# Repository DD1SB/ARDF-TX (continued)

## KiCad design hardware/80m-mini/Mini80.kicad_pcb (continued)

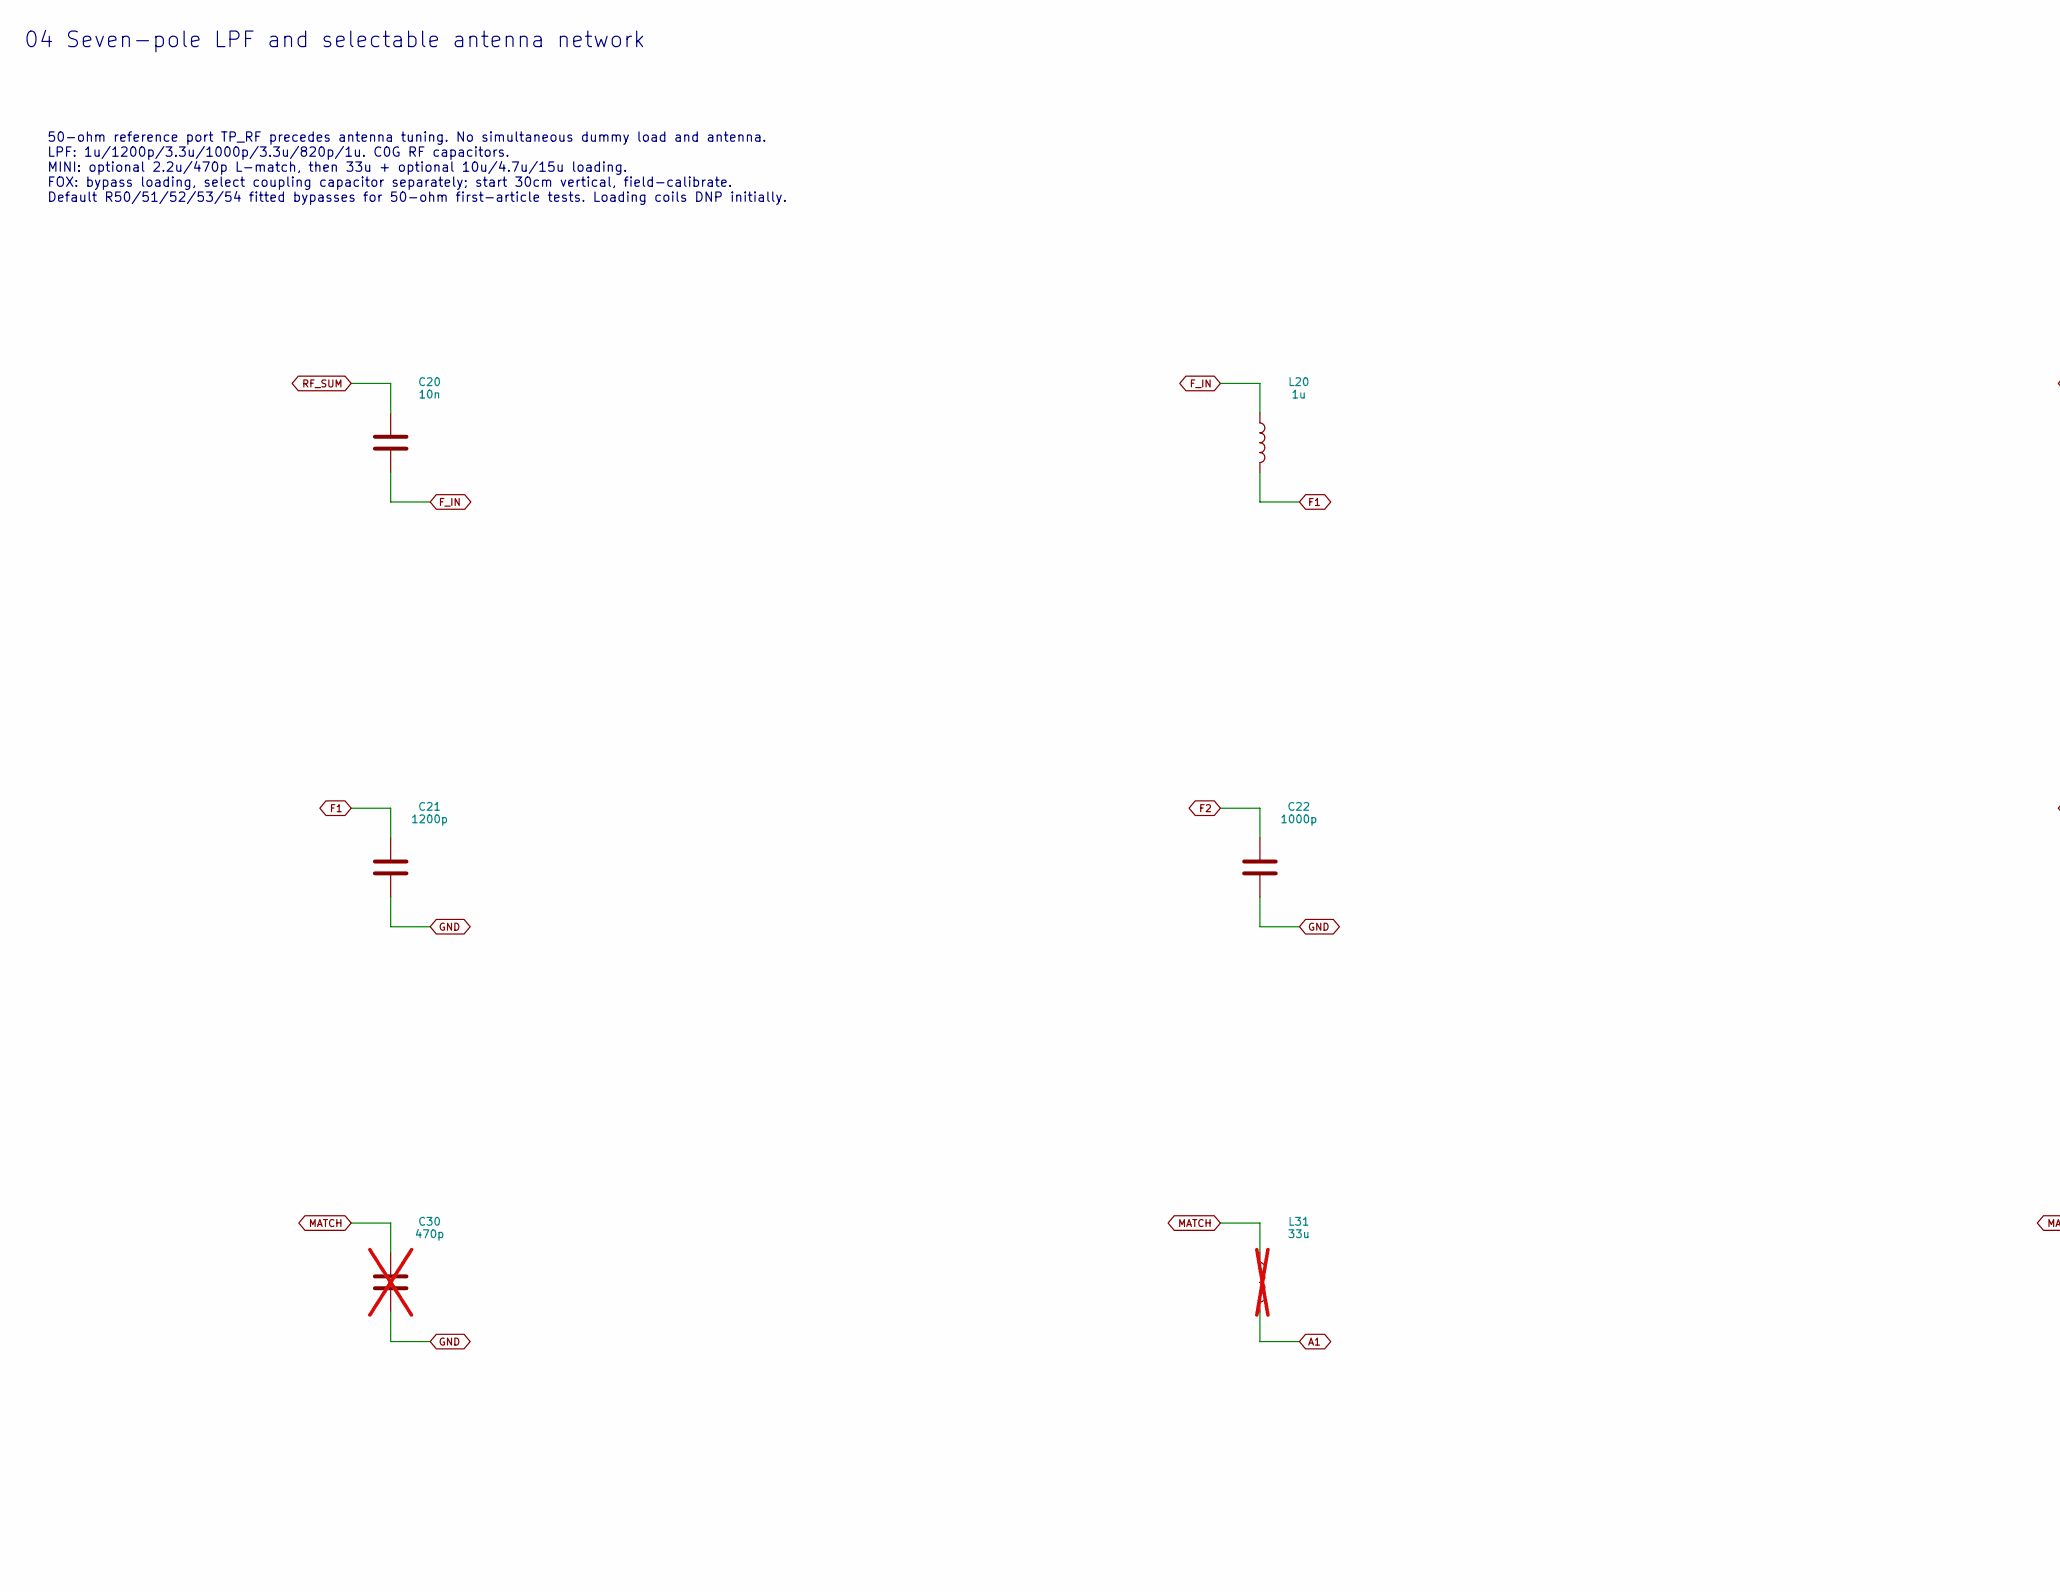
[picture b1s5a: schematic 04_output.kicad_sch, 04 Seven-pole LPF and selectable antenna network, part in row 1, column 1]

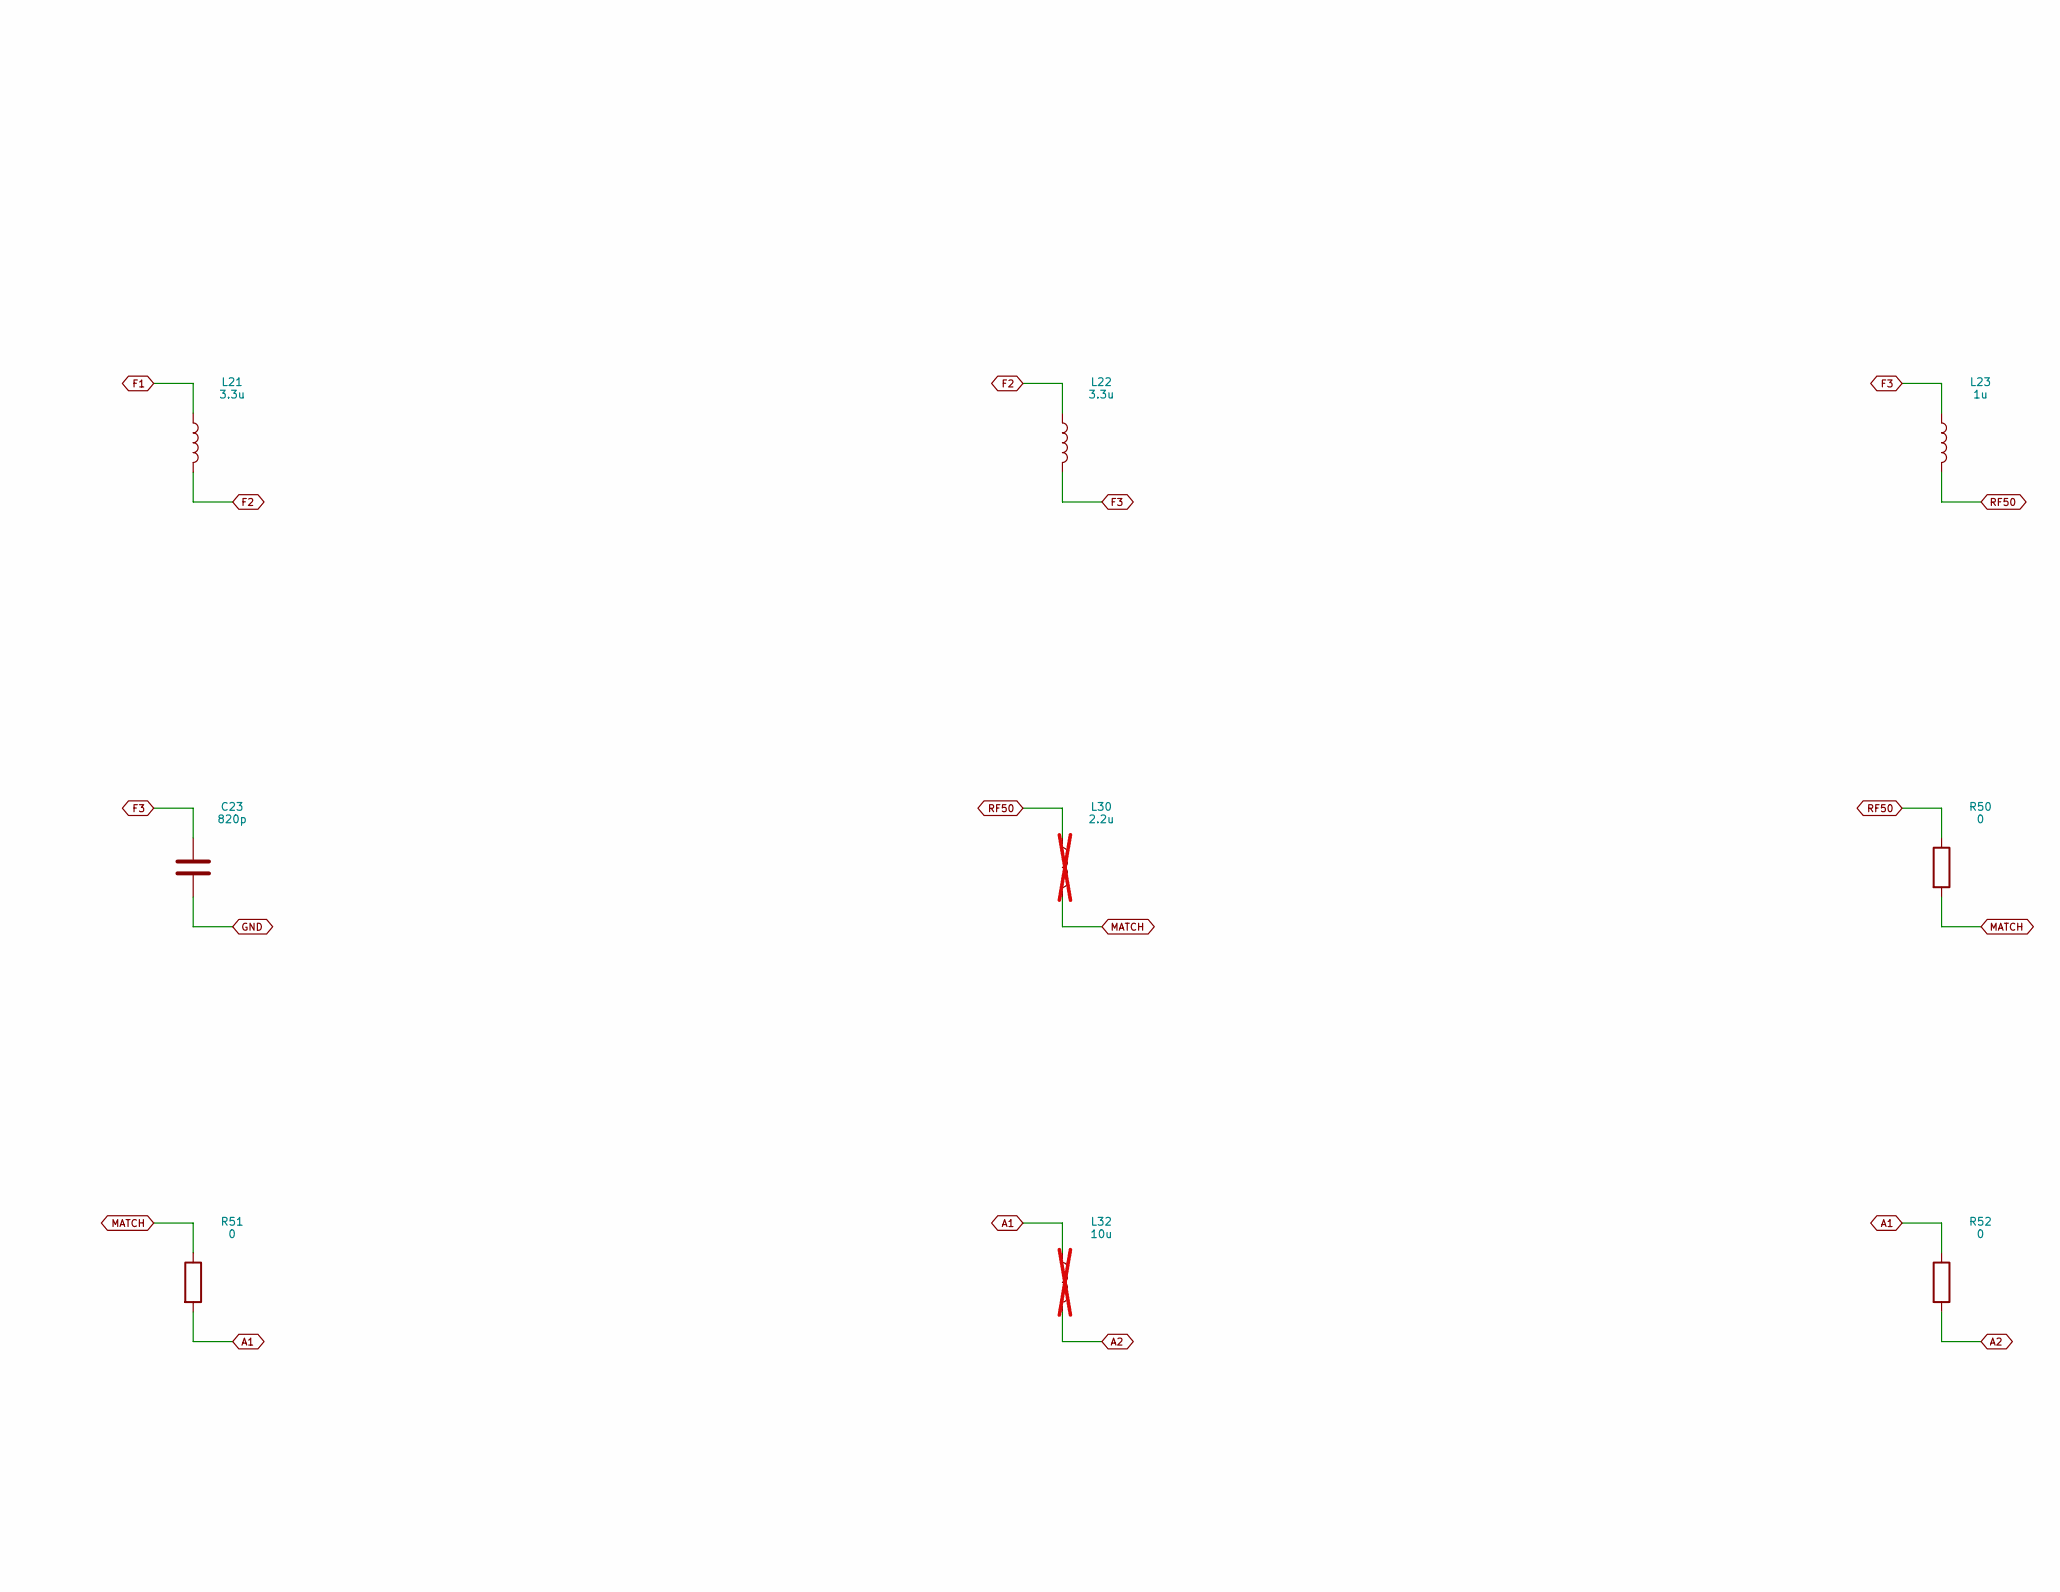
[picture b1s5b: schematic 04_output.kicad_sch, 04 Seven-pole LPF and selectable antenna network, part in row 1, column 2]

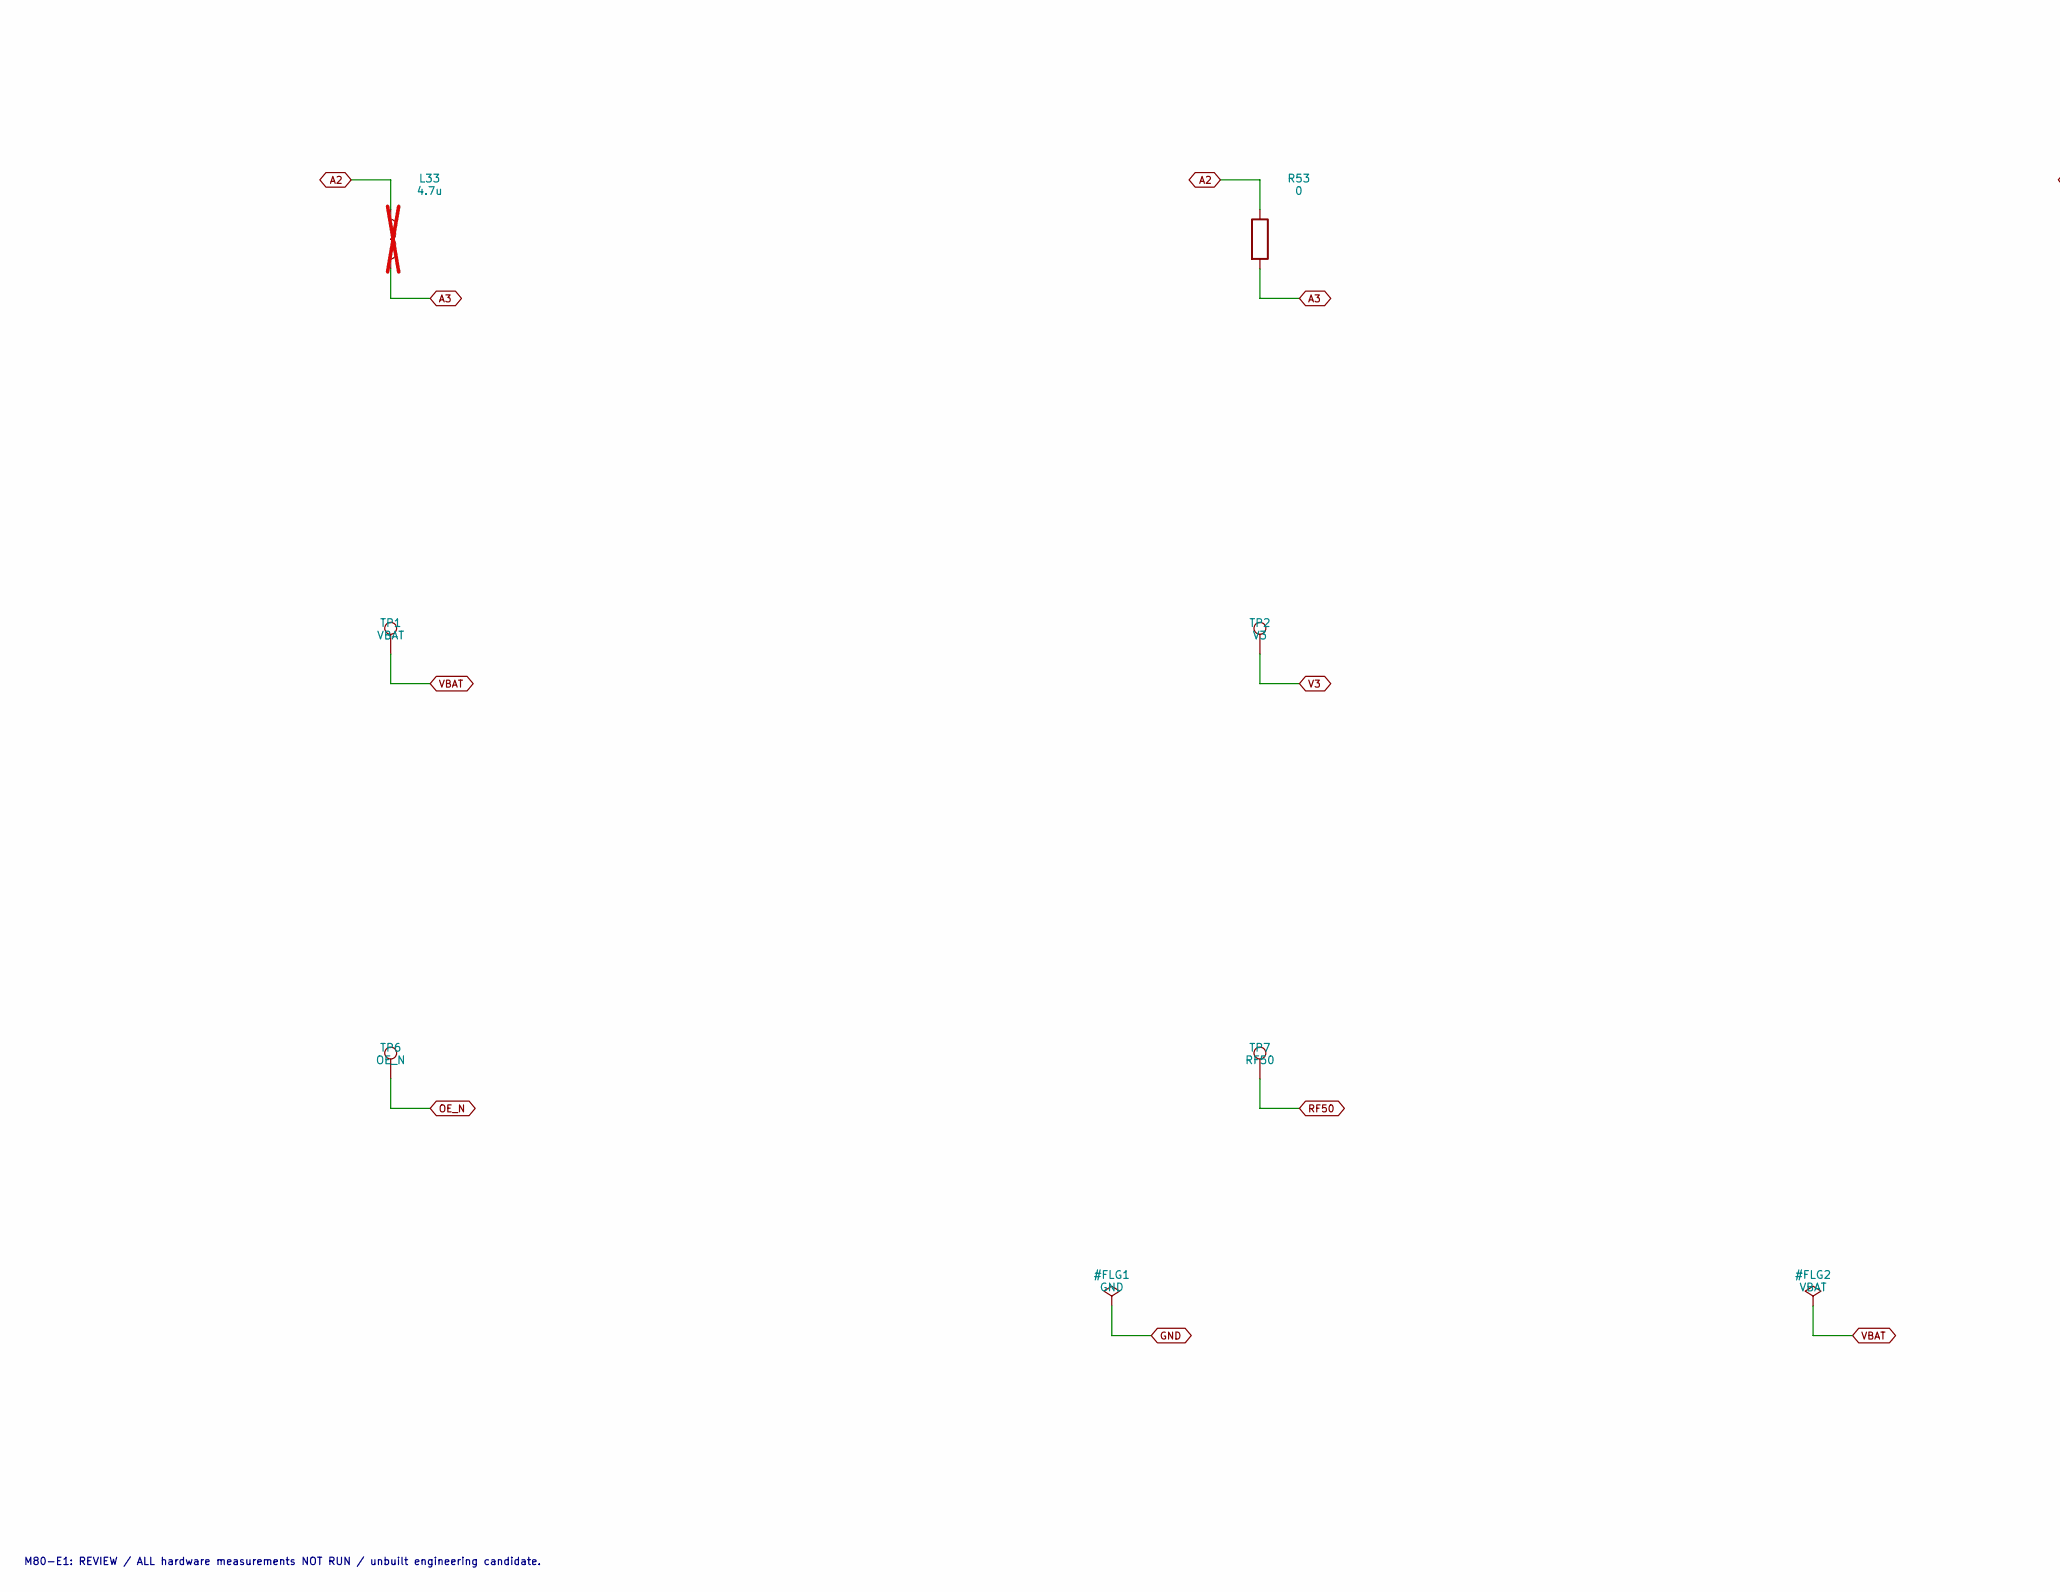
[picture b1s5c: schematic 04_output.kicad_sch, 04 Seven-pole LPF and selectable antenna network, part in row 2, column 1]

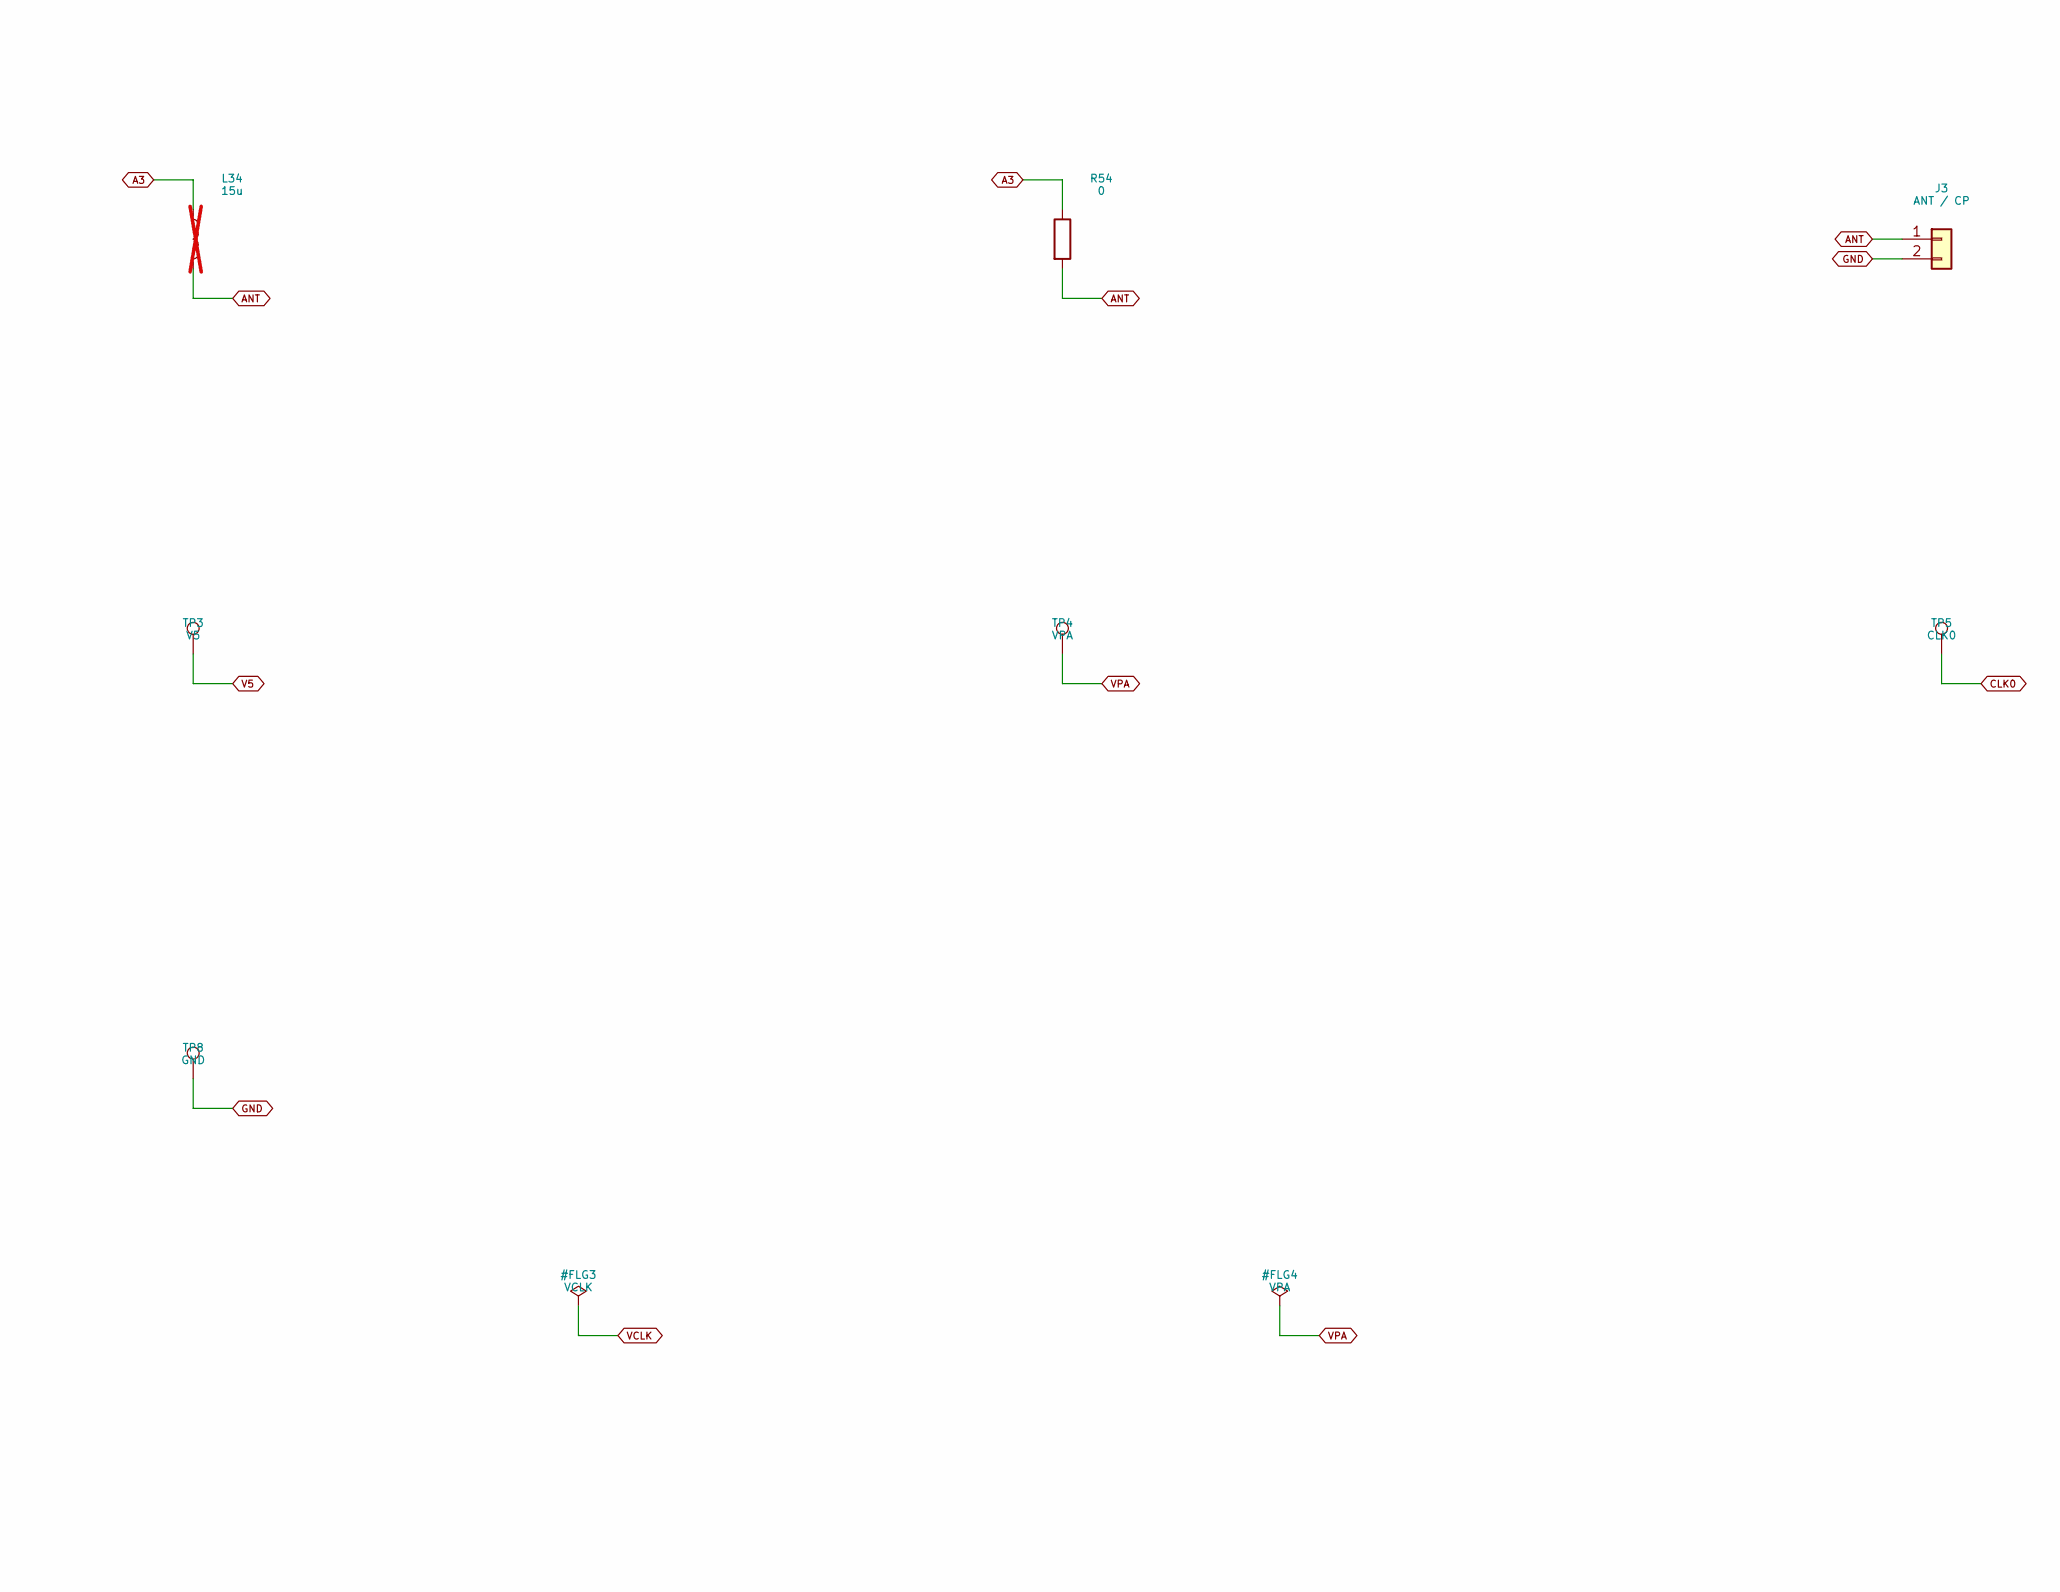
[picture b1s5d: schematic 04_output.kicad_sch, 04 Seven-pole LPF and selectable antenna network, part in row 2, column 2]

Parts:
C20: 10n; C_0603_1608Metric; MPN GRM1885C1H103JA01D
C21: 1200p; C_0603_1608Metric; MPN GRM1885C1H122JA01D
C22: 1000p; C_0603_1608Metric; MPN GRM1885C1H102JA01D
C23: 820p; C_0603_1608Metric; MPN GRM1885C1H821JA01D
C30: 470p; C_0603_1608Metric; MPN GRM1885C1H471JA01D; not fitted
J3: ANT / CP; Wire2; MPN Soldered strain-relieved wire
L20, L23: 1u; Coilcraft_1008LS; MPN 1008LS-102XJRC
L21, L22: 3.3u; Coilcraft_1008LS; MPN 1008LS-332XJRC
L30: 2.2u; Coilcraft_1008LS; MPN 1008LS-222XJRC; not fitted
L31: 33u; Coilcraft_1812LS; MPN 1812LS-333XJRC; not fitted
L32: 10u; Coilcraft_1008LS; MPN 1008LS-103XJRC; not fitted
L33: 4.7u; Coilcraft_1008LS; MPN 1008LS-472XJRC; not fitted
L34: 15u; Coilcraft_1812LS; MPN 1812LS-153XJRC; not fitted
R50, R51, R52, R53, R54: 0; R_0402_1005Metric; MPN RC0402JR-070RL
TP1: VBAT; TestPoint_Pad_D1.0mm; MPN PCB feature
TP2: V3; TestPoint_Pad_D1.0mm; MPN PCB feature
TP3: V5; TestPoint_Pad_D1.0mm; MPN PCB feature
TP4: VPA; TestPoint_Pad_D1.0mm; MPN PCB feature
TP5: CLK0; TestPoint_Pad_D1.0mm; MPN PCB feature
TP6: OE_N; TestPoint_Pad_D1.0mm; MPN PCB feature
TP7: RF50; TestPoint_Pad_D1.0mm; MPN PCB feature
TP8: GND; TestPoint_Pad_D1.0mm; MPN PCB feature

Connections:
A1: L31.2, L32.1, R51.2, R52.1
A2: L32.2, L33.1, R52.2, R53.1
A3: L33.2, L34.1, R53.2, R54.1
ANT: J3.1, L34.2, R54.2
CLK0: TP5.1; also elsewhere on the board
F1: C21.1, L20.2, L21.1
F2: C22.1, L21.2, L22.1
F3: C23.1, L22.2, L23.1
F_IN: C20.2, L20.1
GND: C21.2, C22.2, C23.2, C30.2, J3.2, TP8.1; also elsewhere on the board
MATCH: C30.1, L30.2, L31.1, R50.2, R51.1
OE_N: TP6.1; also elsewhere on the board
RF50: L23.2, L30.1, R50.1, TP7.1
RF_SUM: C20.1; also elsewhere on the board
V3: TP2.1; also elsewhere on the board
V5: TP3.1; also elsewhere on the board
VBAT: TP1.1; also elsewhere on the board
VPA: TP4.1; also elsewhere on the board

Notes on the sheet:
04 Seven-pole LPF and selectable antenna network
50-ohm reference port TP_RF precedes antenna tuning. No simultaneous dummy load and antenna. LPF: 1u/1200p/3.3u/1000p/3.3u/820p/1u. C0G RF capacitors. MINI: optional 2.2u/470p L-match, then 33u + optional 10u/4.7u/15u loading. FOX: bypass loading, select coupling capacitor separately; start 30cm ve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
M80-E1: REVIEW / ALL hardware measurements NOT RUN / unbuilt engineering candidate.

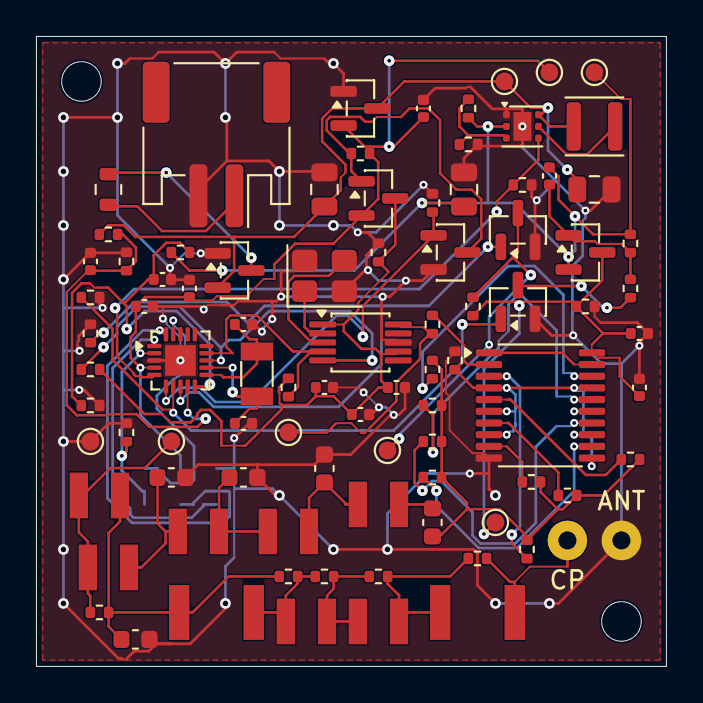
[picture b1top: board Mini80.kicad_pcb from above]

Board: 2 copper layers, 35.0 x 35.0 mm, 92 parts (1 on the bottom side), 51 nets.

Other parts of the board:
H1, H2: MountingHole_2.2mm_M2

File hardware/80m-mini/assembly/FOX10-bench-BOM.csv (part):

ref,value,mpn,footprint,population,note,price_basis,supplier,source_url
J1,BAT 1S,S2B-PH-SM4-TB(LF)(SN),Connector_JST:JST_PH_S2B-PH-SM4-TB_1x02-1MP_P2.00mm_Horizontal,ALL,Pin 1 +. Verify purchased battery harness polarity.,"BUDGET ALLOWANCE, NOT A QUOTE",OPEN,
F1,200mA PPTC,MF-FSMF020X-2,Mini80:MF_FSMF0603,ALL,200 mA hold / protected cell remains mandatory.,CATALOG OBSERVATION,DigiKey,https://www.digikey.com/en/products/detail/bourns-inc/MF-FSM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
Q1,DMP2035U,DMP2035U-7,Package_TO_SOT_SMD:SOT-23,ALL,"Reverse polarity: drain battery, source protected rail.",CATALOG OBSERVATION,LCSC C110499,https://lcsc.com/product-detail/MOSFETs_Diodes-Incorporated-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
C1,10u,GRM21BR61C106KE15L,Capacitor_SMD:C_0805_2012Metric,ALL,,"BUDGET ALLOWANCE, NOT A QUOTE",OPEN,
U1,MCP1700 3.0V,MCP1700T-3002E/TT,Package_TO_SOT_SMD:SOT-23,ALL,1.6 uA typical IQ; 6 V maximum supply.,CATALOG OBSERVATION,LCSC C62244,https://www.lcsc.com/product-image/C62244.html
C2,1u,GRM155R61A105KE15D,Capacitor_SMD:C_0402_1005Metric,ALL,,"BUDGET ALLOWANCE, NOT A QUOTE",OPEN,
U2,TPS61099DRVR,TPS61099DRVR,Package_SON:WSON-6-1EP_2x2mm_P0.65mm_EP1x1.6mm,ALL,"1V feedback; 390k/100k gives 4.90V PWM, ~5.05V PFM.",CATALOG OBSERVATION,LCSC C2842395,https://www.lcsc.com/product-image/C2842395.html
L1,2.2u power,SWPA3015S2R2MT,Inductor_SMD:L_Sunlord_SWPA3015S,ALL,"2.2 uH, saturation >=1.5 A. Short boost loop.","BUDGET ALLOWANCE, NOT A QUOTE",OPEN,
C3,10u,GRM21BR61C106KE15L,Capacitor_SMD:C_0805_2012Metric,ALL,,"BUDGET ALLOWANCE, NOT A QUOTE",OPEN,
C4,22u,GRM21BR61A226ME44L,Capacitor_SMD:C_0805_2012Metric,ALL,Derated effective capacitance must exceed 8uF.,"BUDGET ALLOWANCE, NOT A QUOTE",OPEN,
R1,390k,RC0402FR-07390KL,Resistor_SMD:R_0402_1005Metric,ALL,,"BUDGET ALLOWANCE, NOT A QUOTE",OPEN,
R2,100k,RC0402FR-07100KL,Resistor_SMD:R_0402_1005Metric,ALL,,"BUDGET ALLOWANCE, NOT A QUOTE",OPEN,
R3,100k,RC0402FR-07100KL,Resistor_SMD:R_0402_1005Metric,ALL,,"BUDGET ALLOWANCE, NOT A QUOTE",OPEN,
Q2,CLOCK supply,DMP2035U-7,Package_TO_SOT_SMD:SOT-23,ALL,,CATALOG OBSERVATION,LCSC C110499,https://lcsc.com/product-detail/MOSFETs_Diodes-Incorporated-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
R4,100k,RC0402FR-07100KL,Resistor_SMD:R_0402_1005Metric,ALL,,"BUDGET ALLOWANCE, NOT A QUOTE",OPEN,
Q3,CLOCK enable,"2N7002,215",Package_TO_SOT_SMD:SOT-23,ALL,,"BUDGET ALLOWANCE, NOT A QUOTE",OPEN,https://assets.nexperia.com/documents/data-sheet/2N7002.pdf
R5,100k,RC0402FR-07100KL,Resistor_SMD:R_0402_1005Metric,ALL,,"BUDGET ALLOWANCE, NOT A QUOTE",OPEN,
R6,100k,RC0402FR-07100KL,Resistor_SMD:R_0402_1005Metric,ALL,Discharge clock rail after shutdown.,"BUDGET ALLOWANCE, NOT A QUOTE",OPEN,
R7,2M,RC0402FR-072ML,Resistor_SMD:R_0402_1005Metric,ALL,,"BUDGET ALLOWANCE, NOT A QUOTE",OPEN,
R8,1M,RC0402FR-071ML,Resistor_SMD:R_0402_1005Metric,ALL,,"BUDGET ALLOWANCE, NOT A QUOTE",OPEN,
C5,10n,GRM155R71H103KA88D,Capacitor_SMD:C_0402_1005Metric,ALL,Use internal 1.5V reference; long acquisition; VBAT=3*Vadc.,"BUDGET ALLOWANCE, NOT A QUOTE",OPEN,
U3,ATtiny1616-MNR,ATTINY1616-MNR,Mini80:ATtiny1616_VQFN20_JLC,ALL,,CATALOG OBSERVATION,Mouser,https://www.mouser.com/en/ProductDetail/Microchip-Technology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
C6,100n,CL05B104KO5NNNC,Capacitor_SMD:C_0402_1005Metric,ALL,,CATALOG OBSERVATION,LCSC C1525,https://www.lcsc.com/de/product-detail/C1525.html
C7,1u,GRM155R61A105KE15D,Capacitor_SMD:C_0402_1005Metric,ALL,,"BUDGET ALLOWANCE, NOT A QUOTE",OPEN,
Y1,32.768k 12.5pF,ABS07-32.768KHZ-T,Crystal:Crystal_SMD_3215-2Pin_3.2x1.5mm,ALL,20ppm initial. Load capacitors include AVR ~5.5pF pin capacitance.,CATALOG OBSERVATION,Mouser,https://www.mouser.com/en/ProductDetail/ABRACON/ABS07-32.768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
C8,18p,GRM1555C1H180JA01D,Capacitor_SMD:C_0402_1005Metric,ALL,Initial 18pF: adjust after load/frequency measurement.,"BUDGET ALLOWANCE, NOT A QUOTE",OPEN,
C9,18p,GRM1555C1H180JA01D,Capacitor_SMD:C_0402_1005Metric,ALL,Initial 18pF: effective CL approximately 12.5pF with parasitics.,"BUDGET ALLOWANCE, NOT A QUOTE",OPEN,
R9,100k,RC0402FR-07100KL,Resistor_SMD:R_0402_1005Metric,ALL,,"BUDGET ALLOWANCE, NOT A QUOTE",OPEN,
R10,100k,RC0402FR-07100KL,Resistor_SMD:R_0402_1005Metric,ALL,,"BUDGET ALLOWANCE, NOT A QUOTE",OPEN,
R11,100k,RC0402FR-07100KL,Resistor_SMD:R_0402_1005Metric,ALL,,"BUDGET ALLOWANCE, NOT A QUOTE",OPEN,
R12,390k,RC0402FR-07390KL,Resistor_SMD:R_0402_1005Metric,ALL,,"BUDGET ALLOWANCE, NOT A QUOTE",OPEN,
R13,100k,RC0402FR-07100KL,Resistor_SMD:R_0402_1005Metric,ALL,,"BUDGET ALLOWANCE, NOT A QUOTE",OPEN,
C10,10n,GRM155R71H103KA88D,Capacitor_SMD:C_0402_1005Metric,ALL,,"BUDGET ALLOWANCE, NOT A QUOTE",OPEN,
U4,Si5351A-B-GT,SI5351A-B-GT,Package_SO:MSOP-10_3x3mm_P0.5mm,ALL,Default unprogrammed SKU; do not substitute preprogrammed -Bxxxxx types.,CATALOG OBSERVATION,DigiKey,https://www.digikey.com/en/products/detail/skyworks-solution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
Y2,25MHz 10pF,CX3225FB25000F0FZZH1,Crystal:Crystal_SMD_3225-4Pin_3.2x2.5mm,ALL,10pF CL; Si5351 internal load set to 10pF. Verify total error <50ppm.,CATALOG OBSERVATION,Mouser,https://www.mouser.com/ProductDetail/KYOCERA-AVX/CX3225FB250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
C11,100n,CL05B104KO5NNNC,Capacitor_SMD:C_0402_1005Metric,ALL,,CATALOG OBSERVATION,LCSC C1525,https://www.lcsc.com/de/product-detail/C1525.html
C12,100n,CL05B104KO5NNNC,Capacitor_SMD:C_0402_1005Metric,ALL,,CATALOG OBSERVATION,LCSC C1525,https://www.lcsc.com/de/product-detail/C1525.html
C13,1u,GRM155R61A105KE15D,Capacitor_SMD:C_0402_1005Metric,ALL,,"BUDGET ALLOWANCE, NOT A QUOTE",OPEN,
R14,4.7k,RC0402FR-074K7L,Resistor_SMD:R_0402_1005Metric,ALL,,"BUDGET ALLOWANCE, NOT A QUOTE",OPEN,
R15,4.7k,RC0402FR-074K7L,Resistor_SMD:R_0402_1005Metric,ALL,,"BUDGET ALLOWANCE, NOT A QUOTE",OPEN,
R16,1k,RC0402FR-071KL,Resistor_SMD:R_0402_1005Metric,ALL,Limits input-clamp current during envelope decay. RF_CLK has eight HCT inputs: verify rise/fall timing.,"BUDGET ALLOWANCE, NOT A QUOTE",OPEN,
R17,100k,RC0402FR-07100KL,Resistor_SMD:R_0402_1005Metric,ALL,,"BUDGET ALLOWANCE, NOT A QUOTE",OPEN,
Q4,RF envelope pass,DMP2035U-7,Package_TO_SOT_SMD:SOT-23,ALL,"100k/100k +47nF gate ramp, Vgs final approx -2.5V. Bench-set envelope.",CATALOG OBSERVATION,LCSC C110499,https://lcsc.com/product-detail/MOSFETs_Diodes-Incorporated-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
R18,100k,RC0402FR-07100KL,Resistor_SMD:R_0402_1005Metric,ALL,,"BUDGET ALLOWANCE, NOT A QUOTE",OPEN,
R19,100k,RC0402FR-07100KL,Resistor_SMD:R_0402_1005Metric,ALL,,"BUDGET ALLOWANCE, NOT A QUOTE",OPEN,
C14,47n,GRM155R71C473KA01D,Capacitor_SMD:C_0402_1005Metric,ALL,,"BUDGET ALLOWANCE, NOT A QUOTE",OPEN,
Q5,Envelope drive,"2N7002,215",Package_TO_SOT_SMD:SOT-23,ALL,,"BUDGET ALLOWANCE, NOT A QUOTE",OPEN,
R20,1k,RC0402FR-071KL,Resistor_SMD:R_0402_1005Metric,ALL,Discharges VPA; includes 5mA on-state overhead.,"BUDGET ALLOWANCE, NOT A QUOTE",OPEN,
Q6,RF enable,"2N7002,215",Package_TO_SOT_SMD:SOT-23,ALL,,"BUDGET ALLOWANCE, NOT A QUOTE",OPEN,
R21,100k,RC0402FR-07100KL,Resistor_SMD:R_0402_1005Metric,ALL,"Pull-up follows VPA, preventing disabled-domain backfeeding.","BUDGET ALLOWANCE, NOT A QUOTE",OPEN,
U5,"74HCT240PW,118","74HCT240PW,118",Package_SO:TSSOP-20_4.4x6.5mm_P0.65mm,ALL,TSSOP selected for small-quantity availability. RF power remains a model estimate.,CATALOG OBSERVATION,Mouser,https://www.mouser.com/ProductDetail/Nexperia/74HCT240PW118?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
C15,100n,CL05B104KO5NNNC,Capacitor_SMD:C_0402_1005Metric,ALL,,CATALOG OBSERVATION,LCSC C1525,https://www.lcsc.com/de/product-detail/C1525.html
C16,1u,GRM155R61A105KE15D,Capacitor_SMD:C_0402_1005Metric,ALL,,"BUDGET ALLOWANCE, NOT A QUOTE",OPEN,
R31,560,RC0402FR-07560RL,Resistor_SMD:R_0402_1005Metric,ALL,FOX10: replace all eight with 560 ohm; calibrate measured output.,"BUDGET ALLOWANCE, NOT A QUOTE",OPEN,
R32,560,RC0402FR-07560RL,Resistor_SMD:R_0402_1005Metric,ALL,FOX10: replace all eight with 560 ohm; calibrate measured output.,"BUDGET ALLOWANCE, NOT A QUOTE",OPEN,
R33,560,RC0402FR-07560RL,Resistor_SMD:R_0402_1005Metric,ALL,FOX10: replace all eight with 560 ohm; calibrate measured output.,"BUDGET ALLOWANCE, NOT A QUOTE",OPEN,
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
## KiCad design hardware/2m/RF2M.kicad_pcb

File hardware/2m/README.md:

# RF2M — M5B-E6R2 controlled evaluation candidate

Open [RF2M.kicad_pro](RF2M.kicad_pro). The current, independently reviewed
M5B-E6R2 evaluation candidate is a 150×110 mm, two-layer project. It implements
carrier-keyed A2A Architecture C and one supported SK81 100 SA cooler
for Q501/Q401/Q402. The 20-pin controller contract and critical RF routing are
preserved. Controller M6-L2 and RF80 are unchanged.

Read the [review decision](../../docs/M5B_E6R2_REVIEW_DECISION.md),
[implementation](../../docs/M5B_E6R2_IMPLEMENTATION.md),
[mechanical assembly](../../docs/M5B_E6R2_MECHANICAL_ASSEMBLY.md),
[manufacturing](../../docs/M5B_E6R2_MANUFACTURING.md) and
[first-article plan](../../docs/M5B_E6R2_FIRST_ARTICLE_TEST.md).
The [review package](review/M5B-E6R2/README.md) contains fresh native/CAD evidence,
Gerbers,separate drills,full top stencil,3D views,STEP assembly and all populations.

Independent review found no concrete blocker for **five bare evaluation PCBs**.
Physical RF, thermal and operational qualification remains **NOT_RUN**, and
target firmware integration remains incomplete. No board or stencil has been
ordered and no hardware energized. See the [final reproduction/publication record](../../docs/M5B_E6R2_FINAL_PUBLICATION.md).

- [Five-board fabrication ZIP](review/M5B-E6R2/fabrication/RF2M-M5B-E6R2_JLCPCB_5boards.zip).
- [Full top stencil](review/M5B-E6R2/fabrication/RF2M-M5B-E6R2_FULL_TOP_STENCIL.zip).
- [Mechanical STEP assembly](review/M5B-E6R2/mechanical/complete-mechanical-stack.step).

[E5 review/manufacturing](review/M5B-E5/README.md),[E6](review/M5B-E6/README.md)
and[E6R1](review/M5B-E6R1/README.md) remain immutable. A starting E5native snapshot
is additionally preserved in the E6R2 review package. Use the current
[reproduction procedure](review/M5B-E6R2/REPRODUCE.md),not old CAD-generation
commands against this updated native project.

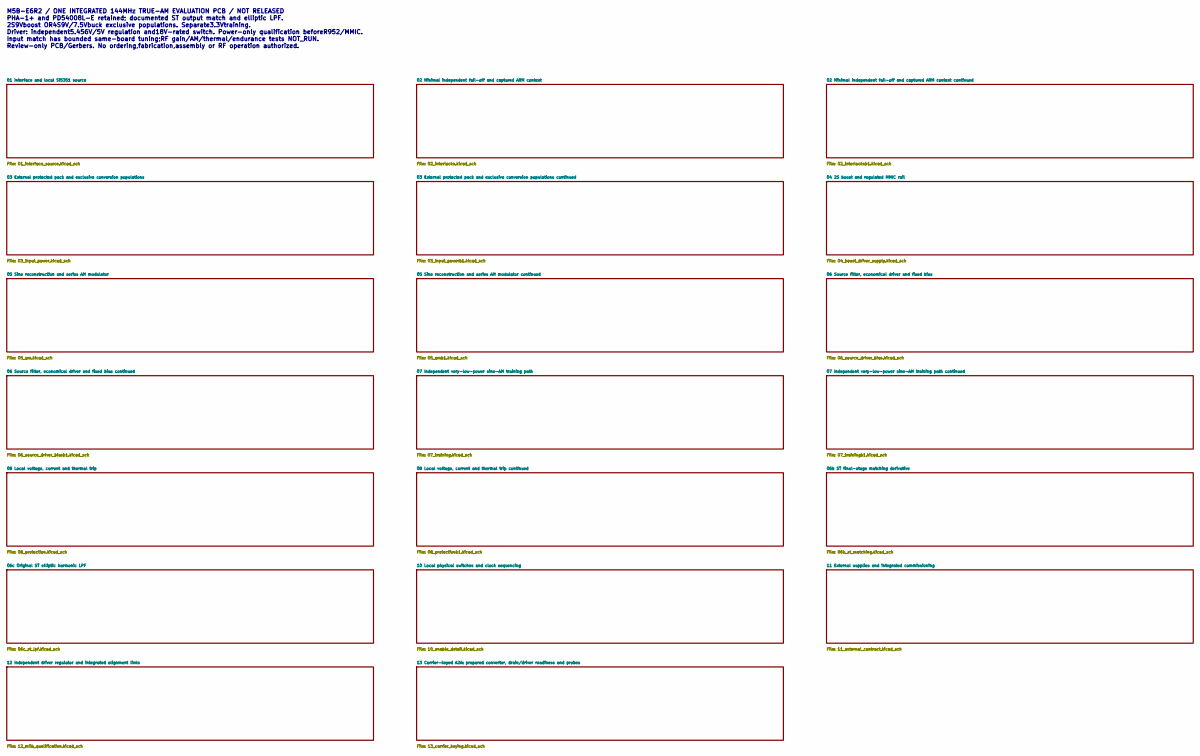
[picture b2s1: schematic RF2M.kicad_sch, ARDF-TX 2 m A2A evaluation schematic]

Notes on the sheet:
M5B-E6R2 / ONE INTEGRATED 144MHz TRUE-AM EVALUATION PCB / NOT RELEASED PHA-1+ and PD54008L-E retained; documented ST output match and elliptic LPF. 2S9Vboost OR4S9V/7.5Vbuck exclusive populations. Separate3.3Vtraining. Driver: independent5.456V/5V regulation and18V-rated switch. Power-only qualific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
